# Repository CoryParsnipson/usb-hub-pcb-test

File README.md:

# usb-hub-pcb-test
Testing PCB creation using KiCAD 5

The usb hub design uses an FE1.1s integrated USB 2.0 controller with the board
layout heavily referenced from https://www.retrocution.com/2020/01/15/easy-diy-tiny-usb-hub-for-raspberry-pi-projects/. Many thanks to Retrocution!

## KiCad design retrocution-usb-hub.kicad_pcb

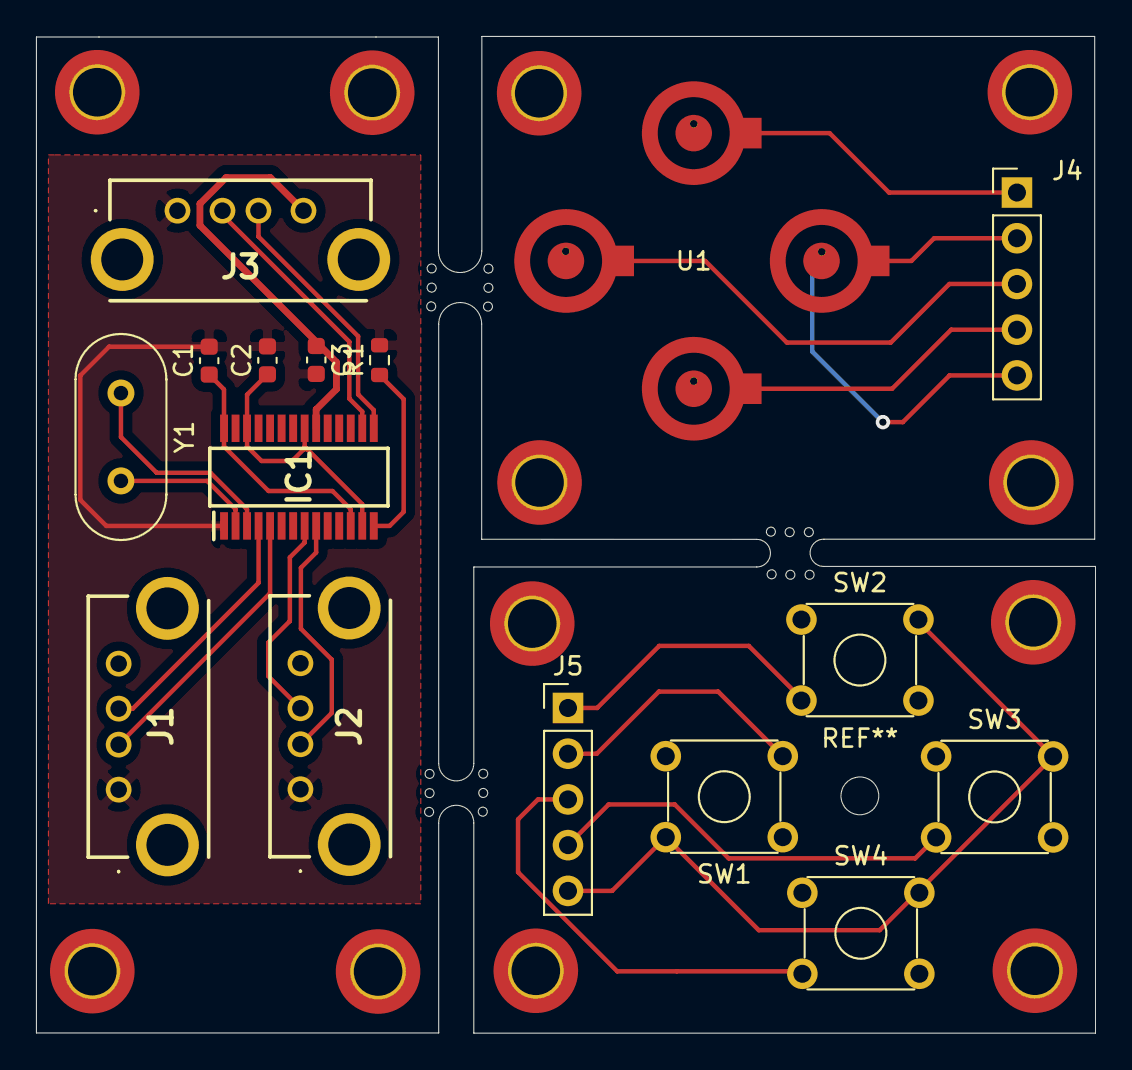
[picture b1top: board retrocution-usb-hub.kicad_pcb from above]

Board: 2 copper layers, 58.8 x 55.4 mm, 16 parts (0 on the bottom side), 23 nets.

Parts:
C1, C2, C3: C; C_0603_1608Metric
IC1: FE1.1S; SOP64P600X175-28N
J1, J2, J3: CU01SAV1S00
J4, J5: Conn_01x05; PinHeader_1x05_P2.54mm_Vertical
R1: R_US; R_0603_1608Metric
SW1, SW2, SW3, SW4: SW_MEC_5G; SW_TH_Tactile_Omron_B3F-10xx
U1: dpad-cross-trace; 3ds_dpad_cross
Y1: Crystal; Crystal_HC49-4H_Vertical

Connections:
+5V: C3.1, IC1.20, J1.4, J2.4, J3.4
/vd18: C1.1, IC1.12, IC1.28
/vd33: C2.1, IC1.13, IC1.21, IC1.26
GND: C1.2, C2.2, C3.2, IC1.1, J1.1, J2.1, J3.1, R1.2
unnamed: IC1.2, Y1.2
unnamed: IC1.3, Y1.1
unnamed: IC1.4, J1.3
unnamed: IC1.5, J1.2
unnamed: IC1.8, J2.3
unnamed: IC1.9, J2.2
unnamed: IC1.14, R1.1
unnamed: IC1.15, J3.3
unnamed: IC1.16, J3.2
unnamed: J4.1, U1.1
unnamed: J4.2, U1.2
unnamed: J4.3, U1.3
unnamed: J4.4, U1.4
unnamed: J4.5, U1.5
unnamed: J5.1, SW2.3
unnamed: J5.2, SW1.3
unnamed: J5.3, SW4.3
unnamed: J5.4, SW3.3
unnamed: J5.5, SW1.2, SW2.2, SW3.2, SW4.2

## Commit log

2021-07-20 Add KiCAD 5.1.x project with completed board draft.
2021-07-20 Add gerber zip files to use github for hosting.
